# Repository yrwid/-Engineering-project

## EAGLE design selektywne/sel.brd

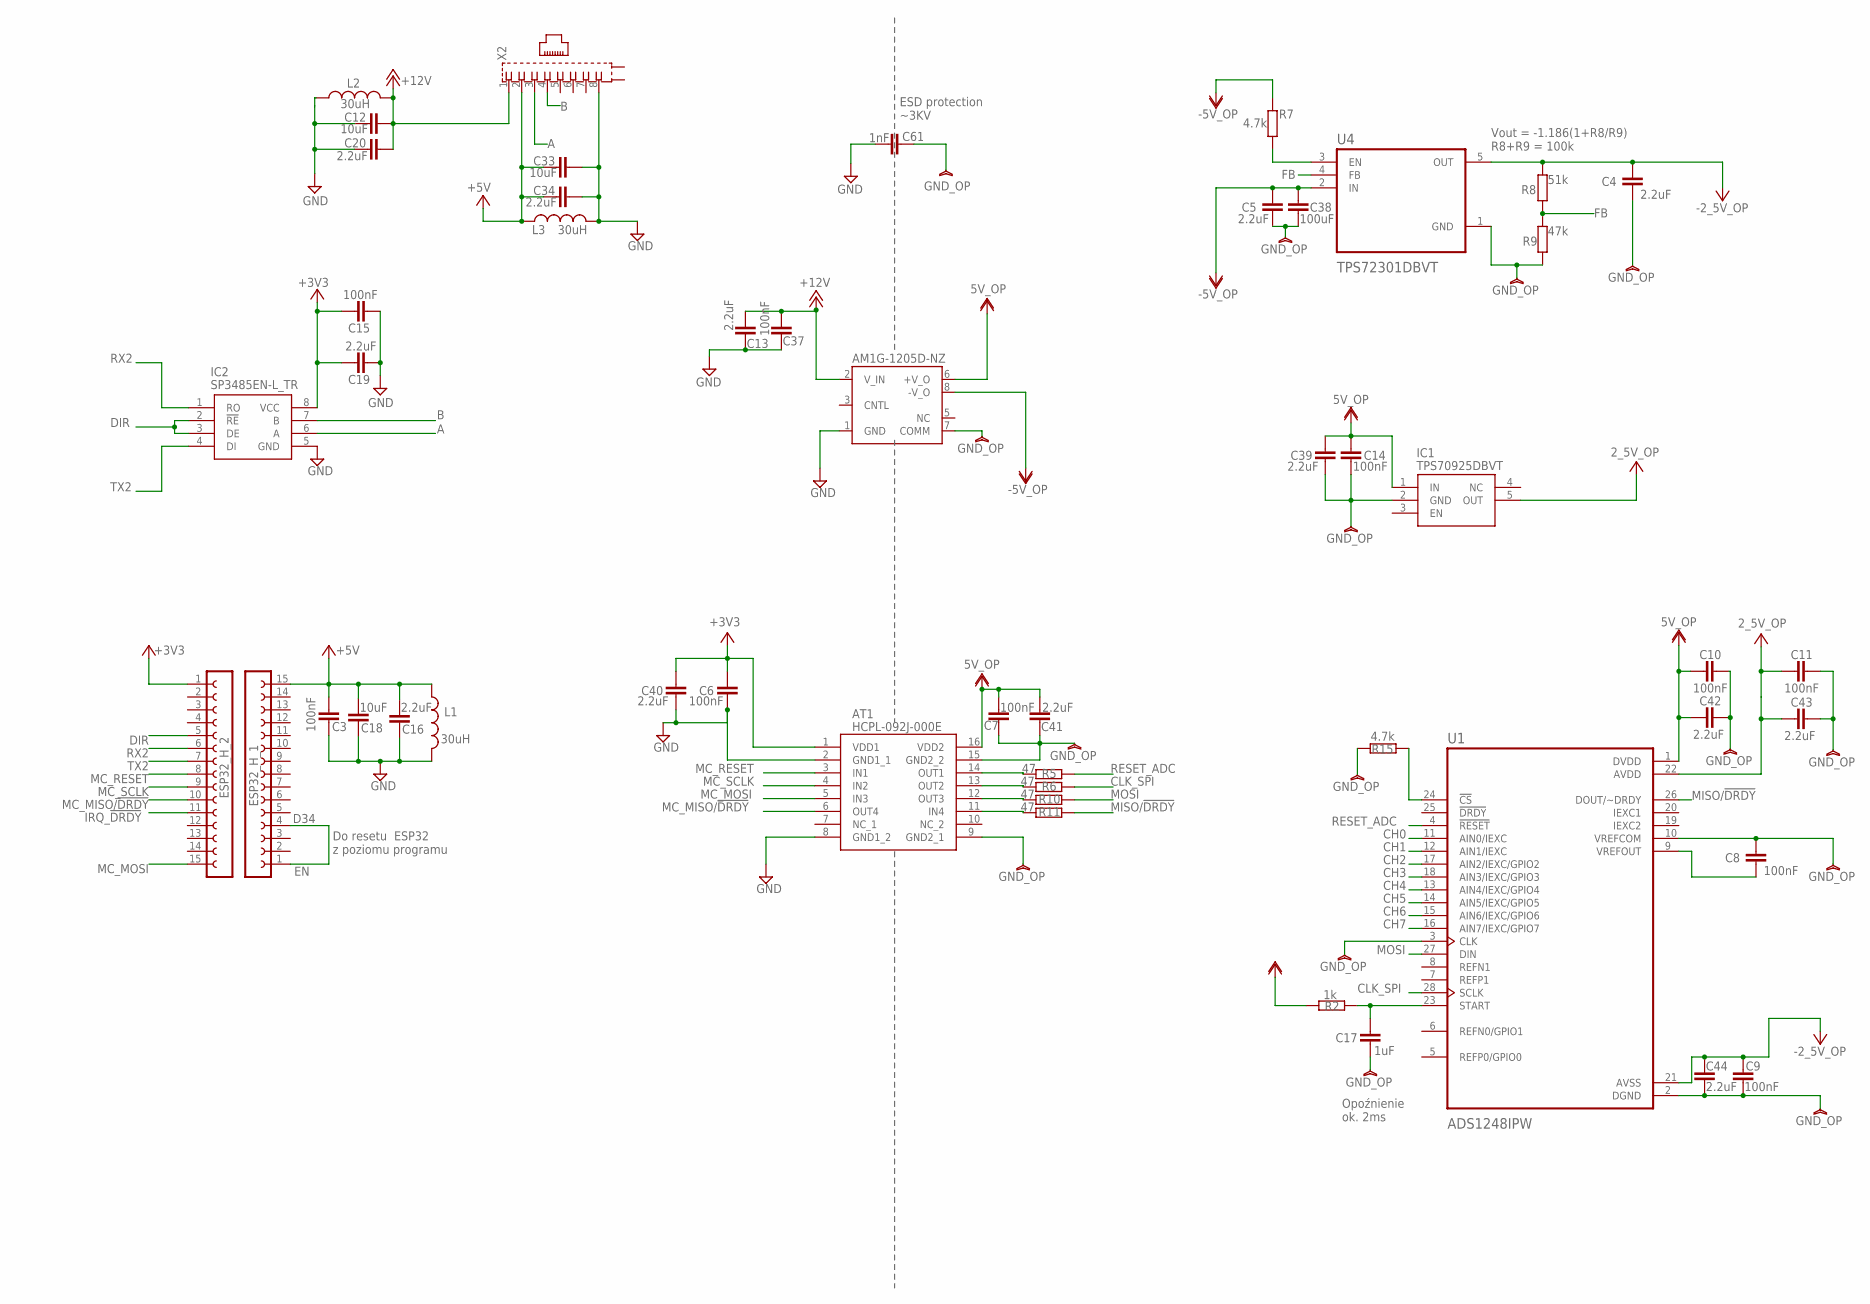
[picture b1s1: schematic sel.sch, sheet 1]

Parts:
AM1G-1205D-NZ: AM1G-1205D-NZ
AT1: HCPL-092J-000E; SOIC127P600X188-16N
C3, C6, C7, C8, C9, C10, C11, C14, C15, C37: 100nF; C1206
C4, C5, C13, C16, C19, C20, C34, C39, C40, C41, C42, C43, C44: 2.2uF; C1206
C12, C18, C33: 10uF; C1206
C17: 1uF; C1206
C38: 100uF; C1206
C61: 1nF; C1206
ESP32_H_1, ESP32_H_2: FE15-1; FE15
IC1: TPS70925DBVT; SOT95P280X145-5N
IC2: SP3485EN-L_TR; SOIC127P600X175-8N
L1, L2, L3: 30uH; 0204/7
R2: 1k; R1206
R5, R6, R10, R11: 47; R1206
R7, R15: 4.7k; R1206
R8: 51k; R1206
R9: 47k; R1206
U1: ADS1248IPW; SOP65P640X120-28N
U4: TPS72301DBVT; SOT95P280X145-5N
X2: 0446200002

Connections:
2_5V_OP: C11.2, C43.2, IC1.5 (OUT), U1.22 (AVDD)
5V_OP: AM1G-1205D-NZ.6 (+V_O), AT1.16 (VDD2), C7.1, C10.2, C14.1, C39.1, C41.1, C42.2, IC1.1 (IN), R2.2, U1.1 (DVDD); also elsewhere on the board
+3V3: AT1.1 (VDD1), C6.2, C15.2, C19.2, C40.2, ESP32_H_2.1, IC2.8 (VCC)
+5V: C3.1, C16.1, C18.1, C33.2, C34.2, ESP32_H_1.15, L1.1, L3.1, X2.2
+12V: AM1G-1205D-NZ.2 (V_IN), C12.1, C13.2, C20.1, C37.2, L2.2, X2.1
-2_5V_OP: C4.1, C9.1, C44.1, R8.2, U1.21 (AVSS), U4.5 (OUT)
-5V_OP: AM1G-1205D-NZ.8 (-V_O), C5.1, C38.1, R7.1, U4.2 (IN); also elsewhere on the board
A: IC2.6 (A), X2.3
B: IC2.7 (B), X2.4
CH0: U1.11 (AIN0/IEXC); also elsewhere on the board
CH1: U1.12 (AIN1/IEXC); also elsewhere on the board
CH2: U1.17 (AIN2/IEXC/GPIO2); also elsewhere on the board
CH3: U1.18 (AIN3/IEXC/GPIO3); also elsewhere on the board
CH4: U1.13 (AIN4/IEXC/GPIO4); also elsewhere on the board
CH5: U1.14 (AIN5/IEXC/GPIO5); also elsewhere on the board
CH6: U1.15 (AIN6/IEXC/GPIO6)
CH7: U1.16 (AIN7/IEXC/GPIO7)
CLK_SPI: AT1.13 (OUT2), R6.2, U1.28 (SCLK)
DIR: ESP32_H_2.5, IC2.2 (!RE), IC2.3 (DE)
EN: ESP32_H_1.1, ESP32_H_1.4
FB: R8.1, R9.2, U4.4 (FB)
GND: AM1G-1205D-NZ.1 (GND), AT1.2 (GND1_1), AT1.8 (GND1_2), C3.2, C6.1, C12.2, C13.1, C15.1, C16.2, C18.2, C19.1, C20.2, C33.1, C34.1, C37.1, C40.1, C61.2, IC2.5 (GND), L1.2, L2.1, L3.2, X2.8
GND_OP: AM1G-1205D-NZ.7 (COMM), AT1.9 (GND2_1), AT1.15 (GND2_2), C4.2, C5.2, C7.2, C8.1, C9.2, C10.1, C11.1, C14.2, C17.2, C38.2, C39.2, C41.2, C42.1, C43.1, C44.2, C61.1, IC1.2 (GND), R9.1, R15.2, U1.2 (DGND), U1.3 (CLK), U1.10 (VREFCOM), U4.1 (GND); also elsewhere on the board
IRQ_!DRDY: ESP32_H_2.11
MC_MISO/!DRDY: AT1.6 (OUT4), ESP32_H_2.10
MC_MOSI: AT1.5 (IN3), ESP32_H_2.15
MC_RESET: AT1.3 (IN1), ESP32_H_2.8
MC_SCLK: AT1.4 (IN2), ESP32_H_2.9
MISO/!DRDY: AT1.11 (IN4), R11.2, U1.26 (DOUT/~DRDY)
MOSI: AT1.12 (OUT3), R10.2, U1.27 (DIN)
unnamed: R7.2, U4.3 (EN)
unnamed: C8.2, U1.9 (VREFOUT)
unnamed: R15.1, U1.24 (!CS)
RESET_ADC: AT1.14 (OUT1), R5.2, U1.4 (!RESET)
RX2: ESP32_H_2.6, IC2.1 (RO)
START: C17.1, R2.1, U1.23 (START)
TX2: ESP32_H_2.7, IC2.4 (DI)

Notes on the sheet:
D34
Vout = -1.186(1+R8/R9) R8+R9 = 100k
Opoźnienie ok. 2ms
Do resetu ESP32 z poziomu programu
ESD protection ~3KV

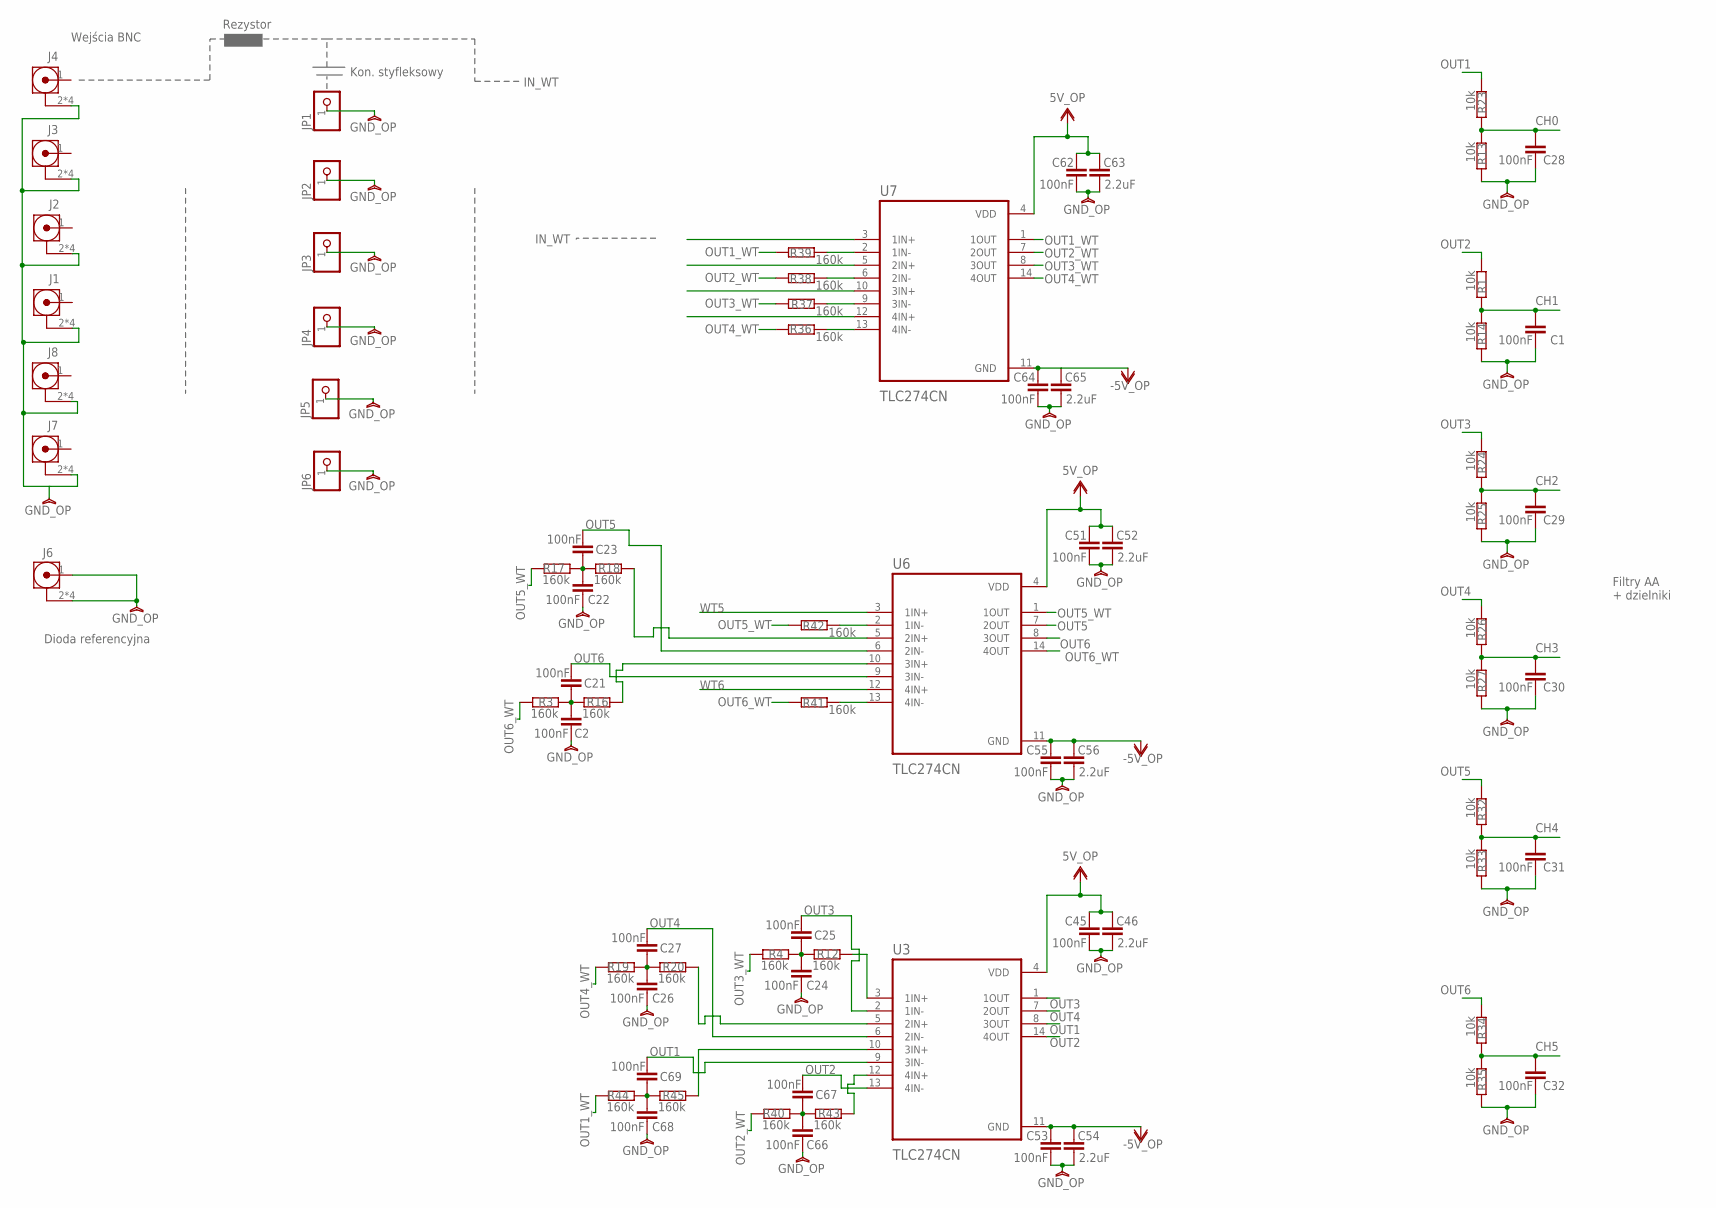
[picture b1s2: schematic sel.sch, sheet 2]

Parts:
C1, C2, C21, C22, C23, C24, C25, C26, C27, C28, C29, C30, C31, C32, C45, C51, C53, C55, C62, C64, C66, C67, C68, C69: 100nF; C1206
C46, C52, C54, C56, C63, C65: 2.2uF; C1206
J1, J2, J3, J4, J6, J7, J8: 5-1634556-0; TE_5-1634556-0
JP1, JP2, JP3, JP4, JP5, JP6: PINHD-1X1; 1X01
R1, R13, R14, R23, R24, R25, R26, R27, R32, R33, R34, R35: 10k; R1206
R3, R4, R12, R16, R17, R18, R19, R20, R36, R37, R38, R39, R40, R41, R42, R43, R44, R45: 160k; R1206
U3, U6, U7: TLC274CN; DIP794W45P254L1969H508Q14

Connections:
1IN+: U7.3 (1IN+)
2IN+: U7.5 (2IN+)
3IN+: U7.10 (3IN+)
3IN+_2: R16.1, U6.10 (3IN+)
4IN+: U7.12 (4IN+)
5V_OP: C45.2, C46.2, C51.2, C52.2, C62.2, C63.2, U3.4 (VDD), U6.4 (VDD), U7.4 (VDD); also elsewhere on the board
-5V_OP: C53.2, C54.2, C55.2, C56.2, C64.2, C65.2, U3.11 (GND), U6.11 (GND), U7.11 (GND); also elsewhere on the board
CH0: C28.1, R13.2, R23.1; also elsewhere on the board
CH1: C1.1, R1.1, R14.2; also elsewhere on the board
CH2: C29.1, R24.1, R25.2; also elsewhere on the board
CH3: C30.1, R26.1, R27.2; also elsewhere on the board
CH4: C31.1, R32.1, R33.2; also elsewhere on the board
CH5: C32.1, R34.1, R35.2; also elsewhere on the board
GND_OP: C1.2, C2.2, C22.2, C24.2, C26.2, C28.2, C29.2, C30.2, C31.2, C32.2, C45.1, C46.1, C51.1, C52.1, C53.1, C54.1, C55.1, C56.1, C62.1, C63.1, C64.1, C65.1, C66.2, C68.2, J1.2, J1.3 (2), J1.4 (2), J1.5 (2), J2.2, J2.3 (2), J2.4 (2), J2.5 (2), J3.2, J3.3 (2), J3.4 (2), J3.5 (2), J4.2, J4.3 (2), J4.4 (2), J4.5 (2), J6.1, J6.2, J6.3 (2), J6.4 (2), J6.5 (2), J7.2, J7.3 (2), J7.4 (2), J7.5 (2), J8.2, J8.3 (2), J8.4 (2), J8.5 (2), JP1.1, JP2.1, JP3.1, JP4.1, JP5.1, JP6.1, R13.1, R14.1, R25.1, R27.1, R33.1, R35.1; also elsewhere on the board
unnamed: R41.1, U6.13 (4IN-)
unnamed: R42.1, U6.2 (1IN-)
unnamed: R18.1, U6.5 (2IN+)
unnamed: C24.1, C25.1, R4.1, R12.2
unnamed: R12.1, U3.3 (1IN+)
unnamed: C26.1, C27.1, R19.1, R20.2
unnamed: R20.1, U3.5 (2IN+)
unnamed: C2.1, C21.1, R3.1, R16.2
unnamed: C66.1, C67.1, R40.1, R43.2
unnamed: C22.1, C23.1, R17.1, R18.2
unnamed: C68.1, C69.1, R44.1, R45.2
unnamed: R43.1, U3.12 (4IN+)
unnamed: R45.1, U3.10 (3IN+)
unnamed: R36.1, U7.13 (4IN-)
unnamed: R37.1, U7.9 (3IN-)
unnamed: R38.1, U7.6 (2IN-)
unnamed: R39.1, U7.2 (1IN-)
OUT1: C69.2, R23.2, U3.8 (3OUT), U3.9 (3IN-)
OUT1_WT: R39.2, R44.2, U7.1 (1OUT)
OUT2: C67.2, R1.2, U3.13 (4IN-), U3.14 (4OUT)
OUT2_WT: R38.2, R40.2, U7.7 (2OUT)
OUT3: C25.2, R24.2, U3.1 (1OUT), U3.2 (1IN-)
OUT3_WT: R4.2, R37.2, U7.8 (3OUT)
OUT4: C27.2, R26.2, U3.6 (2IN-), U3.7 (2OUT)
OUT4_WT: R19.2, R36.2, U7.14 (4OUT)
OUT5: C23.2, R32.2, U6.6 (2IN-), U6.7 (2OUT)
OUT5_WT: R17.2, R42.2, U6.1 (1OUT)
OUT6: C21.2, R34.2, U6.8 (3OUT), U6.9 (3IN-)
OUT6_WT: R3.2, R41.2, U6.14 (4OUT)
WT5: U6.3 (1IN+)
WT6: U6.12 (4IN+)

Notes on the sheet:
Wejścia BNC
Filtry AA + dzielniki
IN_WT
Kon. styfleksowy
Rezystor
Dioda referencyjna

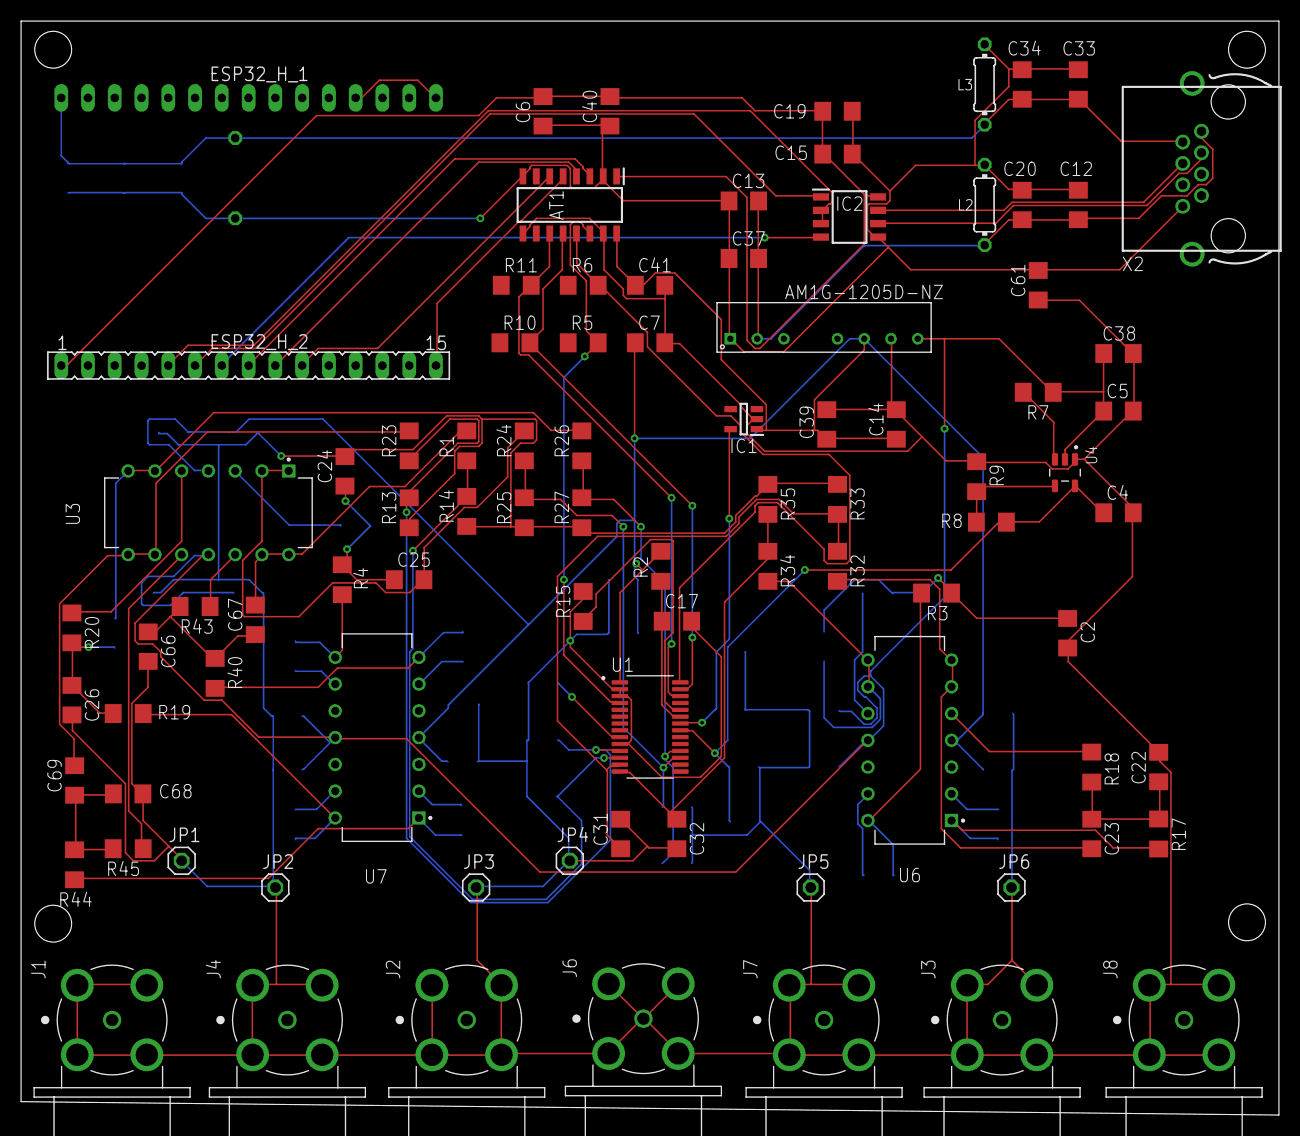
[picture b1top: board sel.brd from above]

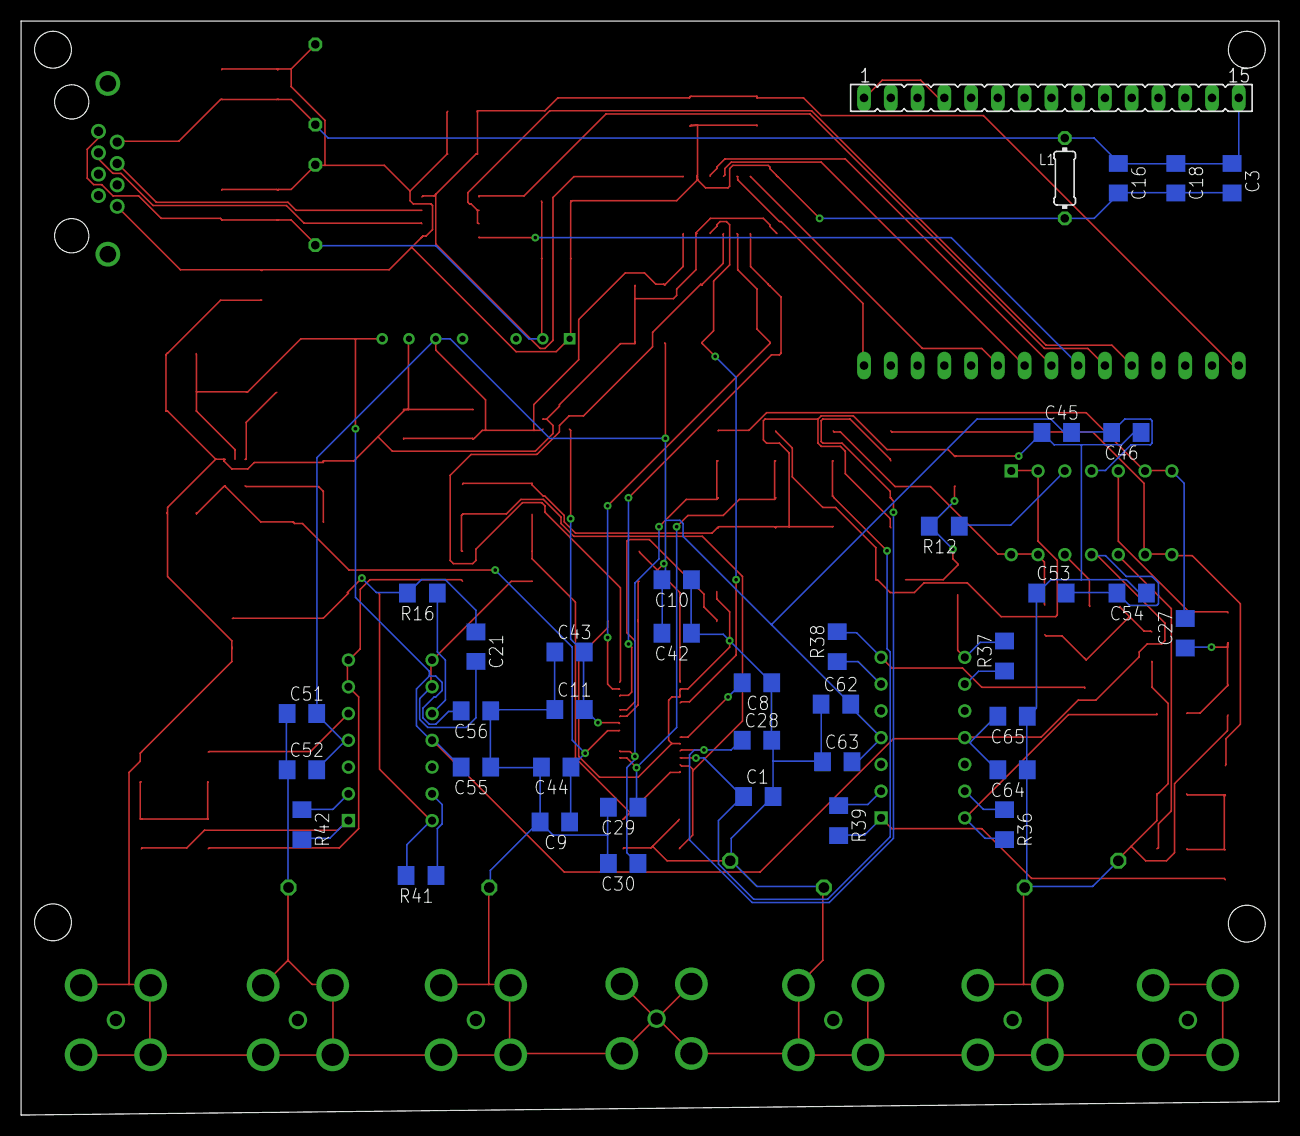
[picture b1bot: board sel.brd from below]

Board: 2 copper layers, 119.4 x 103.8 mm, 126 parts (38 on the bottom side), 64 nets.

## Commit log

2020-09-29 buffer 5 chars and replay
2020-09-30 communication with master(RTU, fuction 3)
2020-10-24 Working modbus, SPI and master for tests
2020-10-24 splited main() onto 2 tasks
2020-10-29 PCB scheme
2020-11-01 fixed power supply
2020-11-04 fixed some errors
2020-11-07 Fixed analog and digital problems,a active filter
2020-11-17 fixes in progress 8/12
2020-11-18 fixes 12/12
2020-11-20 PCB v1
2020-11-20 fux wt problem
